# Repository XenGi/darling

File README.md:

![pcb][pcb]
![3d model front][3d-front]
![3d model back][3d-back]

darling
=======

FTDI helper for the future. With FT230X, blinky lights and USB-C! Also potentially the tinyest USB-C to Serial adapter in the world. :smiley:

__Got a smaller USB-C to serial adapter? Please send me a link!__

BOM
---

| Part                 | Qty | Pkg   | Ref    | Description       | Mouser | LCSC |
| -------------------- | -   | ----- | ------ | ----------------- | ------ | ---- |
| Hirose CX70M-24P1    | 1   | -     | J1     | USB-C Receptacle  | [798-CX70M-24P1](https://eu.mouser.com/ProductDetail/Hirose-Connector/CX70M-24P1?qs=NniTrqY%252BJ%252BUR9QssvRGPwA%3D%3D) | [C778726](https://www.lcsc.com/product-detail/C778726.html) |
| -                    | 1   | -     | J2     | Pin Header        | [571-826947-5](https://eu.mouser.com/ProductDetail/TE-Connectivity/826947-5?qs=xF5SkmKSM76JMcUnQ8djKQ%3D%3D) | [C6332198](https://www.lcsc.com/product-detail/C6332198) |
| FTDI FT230XQ-R       | 1   | QFN16 | U1     | USB-Serial IC     | [895-FT230XQ-R](https://eu.mouser.com/ProductDetail/FTDI/FT230XQ-R?qs=Gp1Yz1mis3VvmXwyDmIHOg%3D%3D) | [C128629](https://www.lcsc.com/product-detail/C128629) |
| -                    | 1   | 0603  | D1     | Red RX LED        | [710-150060GS75000](https://eu.mouser.com/ProductDetail/Wurth-Elektronik/150060GS75000?qs=LlUlMxKIyB0UYkq5lDO8nA%3D%3D) | [C965804](https://www.lcsc.com/product-detail/C965804) |
| -                    | 1   | 0603  | D2     | Green TX LED      | [710-150060RS75000](https://eu.mouser.com/ProductDetail/Wurth-Elektronik/150060RS75000?qs=LlUlMxKIyB3QnmZ3fw%2FVCA%3D%3D) | [C965799](https://www.lcsc.com/product-detail/C965799) |
| -                    | 2   | 0402  | R1, R2 | 27 Ohm Resistor   | [652-CR0402FX-27R0GLF](https://eu.mouser.com/ProductDetail/Bourns/CR0402-FX-27R0GLF?qs=SFHnMgm9IsxG%252BvpJZf0h2g%3D%3D) | [C138021](https://www.lcsc.com/product-detail/C138021) |
| -                    | 2   | 0402  | R3, R4 | 270 Ohm Resistor  | [652-CR0402FX-2700GLF](https://eu.mouser.com/ProductDetail/Bourns/CR0402-FX-2700GLF?qs=SFHnMgm9IsyXrY3JqhOnHQ%3D%3D) | [C163474](https://www.lcsc.com/product-detail/C163474) |
| -                    | 2   | 0402  | R5, R6 | 5.1 kOhm Resistor | [652-CR0402FX-5101GLF](https://eu.mouser.com/ProductDetail/Bourns/CR0402-FX-5101GLF?qs=ePR1ZvdkOKImkuXR%2F%2FtvtA%3D%3D) | [C105873](https://www.lcsc.com/product-detail/C105873) |
| -                    | 1   | 0402  | C1     | 10 nF Capacitor   | [80-C0402C103K3R7867](https://eu.mouser.com/ProductDetail/KEMET/C0402C103K3RAC7867?qs=2QcrrtqkWlmbWpEppaNgjw%3D%3D) | [C272878](https://www.lcsc.com/product-detail/C272878) |
| -                    | 2   | 0402  | C2, C4 | 100 nF Capacitor  | [81-GRM155C71H104JE9J](https://eu.mouser.com/ProductDetail/Murata-Electronics/GRM155C71H104JE19J?qs=QzBtWTOodeUR0Y4f0k0Zww%3D%3D) | [C541464](https://www.lcsc.com/product-detail/C541464) |
| -                    | 1   | 0402  | C3     | 4.7 uF Capacitor  | [81-GRM15C61E475ME15J](https://eu.mouser.com/ProductDetail/Murata-Electronics/GRM155C61E475ME15J?qs=By6Nw2ByBD02p8xq06vhEQ%3D%3D) | [C368809](https://www.lcsc.com/product-detail/C368809) |
| -                    | 2   | 0402  | C5, C6 | 47 pF Capacitor   | [81-GRT1555C1H470FA2D](https://eu.mouser.com/ProductDetail/Murata-Electronics/GRT1555C1H470FA02D?qs=RcG8xmE7yp3he2Sm3%2FOw%252Bg%3D%3D) | [C527009](https://www.lcsc.com/product-detail/C527009) |
| Laird MI0805K601R-10 | 1   | 0805  | FB1    | Ferrite Bead      | [875-MI0805K601R-10](https://eu.mouser.com/ProductDetail/Laird-Performance-Materials/MI0805K601R-10?qs=bbdZqDPQhEXXIHxc191aOg%3D%3D) | [C21286](https://www.lcsc.com/product-detail/C21286) |

See [Octopart][octopart] for a detailed list with links.
With current prices this totals to ~4.50€ just for parts excluding costs for the PCB manufacturing. If you need a PCB, just ask. I have lots of them. :)

Schematics
----------

![schematics][schema]

Create Gerber files
-------------------

Export the gerber and drill files from KiCAD to a subdir like `gerber`. To create a ZIP file with the needed gerber files for a PCB fab:

```
cd gerber
zip darling.zip *.gbr *.drl
```

I recommend [JLCPCB][jlcpcb]. It's the cheapest way to get the PCBs and they offer decent quality.
You can directly order it at [PCBWay][pcbway]. They've got some nice matte black PCBs!
If you want purple PCBs you can also use [OSHPark][oshpark].
If you want it faster and you're in Germany/EU I uploaded it to [Aisler][aisler] to.

[![pcb top][oshpark_darling_top] ![pcb bottom][oshpark_darling_bottom]][oshpark]

---

_Made with :heart: and aliexpress_

[pcb]: https://gitlab.com/xengi/darling/raw/master/darling_pcb.png
[3d-front]: https://gitlab.com/xengi/darling/raw/master/darling_3d_front.png
[3d-back]: https://gitlab.com/xengi/darling/raw/master/darling_3d_back.png
[schema]: https://gitlab.com/xengi/darling/raw/master/darling_schema.png
[octopart]: https://octopart.com/bom-tool/4VikRkAe
[jlcpcb]: https://jlcpcb.com/
[pcbway]: https://www.pcbway.com/project/shareproject/Darling_Rev4_f9889cb6.html
[oshpark_darling_top]: https://644db4de3505c40a0444-327723bce298e3ff5813fb42baeefbaa.ssl.cf1.rackcdn.com/4cf1ffcfeee0332e9eda92195310da6b.png
[oshpark_darling_bottom]: https://644db4de3505c40a0444-327723bce298e3ff5813fb42baeefbaa.ssl.cf1.rackcdn.com/1f266f38a687f960f46bc39729592b03.png
[oshpark]: https://oshpark.com/shared_projects/s8UnAcGC
[aisler]: https://aisler.net/p/NFTQABKA

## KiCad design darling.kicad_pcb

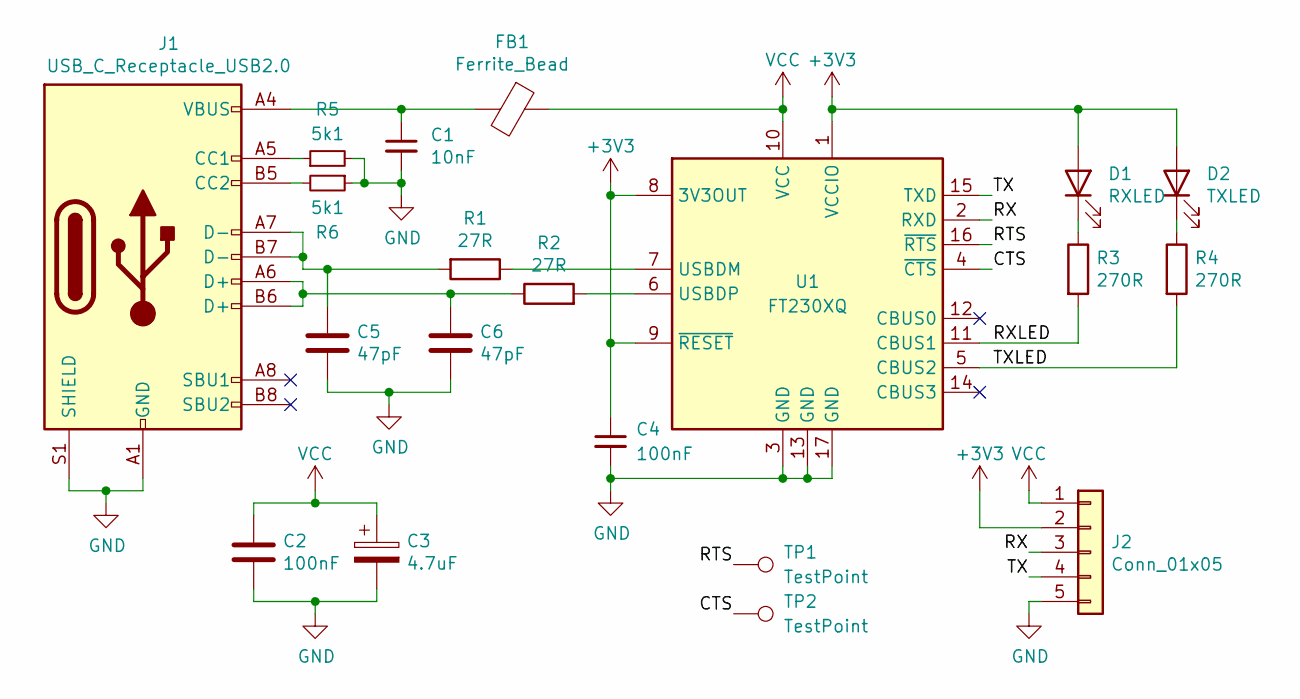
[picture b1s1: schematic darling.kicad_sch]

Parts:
C1: 10nF; C_0402_1005Metric; LCSC C272878
C2, C4: 100nF; C_0402_1005Metric; LCSC C541464
C3: 4.7uF; C_0402_1005Metric; LCSC C368809
C5, C6: 47pF; C_0402_1005Metric; LCSC C527009
D1: RXLED; LED_0603_1608Metric_Pad1.05x0.95mm_HandSolder; LCSC C965804
D2: TXLED; LED_0603_1608Metric_Pad1.05x0.95mm_HandSolder; LCSC C965799
FB1: Ferrite_Bead; L_0805_2012Metric_Pad1.15x1.40mm_HandSolder; LCSC C21286
J1: USB_C_Receptacle_USB2.0; CX70M-24P1; LCSC C778726
J2: Conn_01x05; PinHeader_1x05_P2.54mm_Horizontal; LCSC C6332198
R1, R2: 27R; R_0402_1005Metric; LCSC C138021
R3, R4: 270R; R_0402_1005Metric; LCSC C163474
R5, R6: 5k1; R_0402_1005Metric; LCSC C105873
TP1, TP2: TestPoint; TestPoint_Pad_D1.0mm
U1: FT230XQ; QFN-16-1EP_4x4mm_P0.65mm_EP2.5x2.5mm; LCSC C128629

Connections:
+3V3: C4.1, D1.2 (A), D2.2 (A), J2.2, U1.1 (VCCIO), U1.8 (3V3OUT), U1.9 (~RESET)
/CTS: TP2.1, U1.4 (~CTS)
/RTS: TP1.1, U1.16 (~RTS)
/RX: J2.3, U1.2 (RXD)
/RXLED: R3.2, U1.11 (CBUS1)
/TX: J2.4, U1.15 (TXD)
/TXLED: R4.2, U1.5 (CBUS2)
GND: C1.2, C2.2, C3.2, C4.2, C5.2, C6.2, J1.A1 (GND), J1.A12 (GND), J1.B1 (GND), J1.B12 (GND), J1.S1 (SHIELD), J2.5, R5.2, R6.1, U1.3 (GND), U1.13 (GND), U1.17 (GND)
unnamed: C1.1, FB1.2, J1.A4 (VBUS), J1.A9 (VBUS), J1.B4 (VBUS), J1.B9 (VBUS)
unnamed: C5.1, J1.A7 (D-), J1.B7 (D-), R1.2
unnamed: C6.1, J1.A6 (D+), J1.B6 (D+), R2.1
unnamed: D1.1 (K), R3.1
unnamed: D2.1 (K), R4.1
unnamed: J1.A5 (CC1), R5.1
unnamed: J1.B5 (CC2), R6.2
unnamed: R1.1, U1.7 (USBDM)
unnamed: R2.2, U1.6 (USBDP)
VCC: C2.1, C3.1, FB1.1, J2.1, U1.10 (VCC)

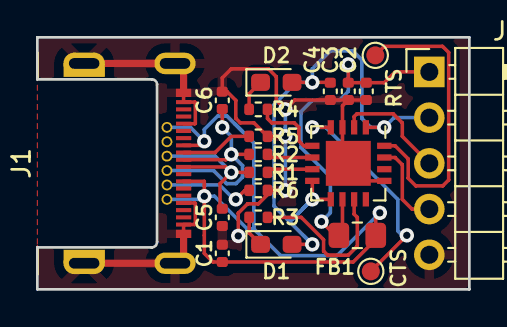
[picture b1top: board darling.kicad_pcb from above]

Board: 2 copper layers, 24.0 x 14.0 mm, 20 parts (0 on the bottom side), 18 nets.

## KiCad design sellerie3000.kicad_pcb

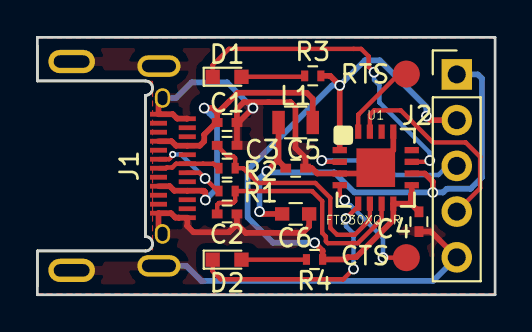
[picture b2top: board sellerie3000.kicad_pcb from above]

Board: 2 copper layers, 25.4 x 14.3 mm, 18 parts (0 on the bottom side), 16 nets.

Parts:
C1: 10nF; C_0402
C2, C3: 47pF; C_0402
C4, C5: 100nF; C_0402
C6: 4.7uF; C_0603
CTS: CTS; Measurement_Point_Round-SMD-Pad_Small
D1: RX; LED_0603
D2: TX; LED_0603
J1: USB_C_Receptacle; DX07B024JJ3
J2: Conn_01x05; Pin_Header_Straight_1x05_Pitch2.54mm
L1: Ferrite_Bead; L_0805
R1, R2: 27R; R_0402
R3, R4: 270R; R_0402
RTS: RTS; Measurement_Point_Round-SMD-Pad_Small
U1: FT230XQ-R; QFN16

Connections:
3V3: C4.1, J2.2, R3.1, R4.1, U1.1, U1.8, U1.9
/CBUS1: D1.1, U1.11
/CBUS2: D2.1, U1.5
/CTS: CTS.1, U1.4
/RTS: RTS.1, U1.16
/USBDM: C2.1, R1.1, U1.7
/USBDP: C3.1, R2.1, U1.6
GND: C1.2, C2.2, C3.2, C4.2, C5.2, C6.2, J1.A1, J1.A12, J1.B1, J1.B12, J1.S1, J2.5, U1.3, U1.13, U1.17
unnamed: C1.1, J1.A4, J1.A9, J1.B4, J1.B9, L1.2
unnamed: D1.2, R3.2
unnamed: D2.2, R4.2
unnamed: J1.A6, J1.B6, R2.2
unnamed: J1.A7, J1.B7, R1.2
RX: J2.3, U1.2
TX: J2.4, U1.15
VCC: C5.1, C6.1, J2.1, L1.1, U1.10

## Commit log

2018-06-17 finished design
2018-06-17 replaced comma with dots
2018-06-24 wow much update many unfinished
2018-06-25 nearly done
2018-06-25 measurements added
2018-10-28 Add LICENSE
2019-03-26 refactured to version 2; new usb receptacle; even tinier
2019-03-26 README updated
2019-03-26 trying to remove the 2nd git repo o0
2019-03-26 begone! strange repo!
2019-03-26 smaler images
2019-03-27 artwork improved
2019-04-19 switched LEDs
2019-04-20 reroute some parts
2019-04-20 changed drc rules
2019-04-20 fixed #4 usb-c is now reversable
2019-04-20 images updates
2019-04-20 removed J1 label
2019-04-20 downsized images
2019-04-20 something changed
2019-04-20 drc runs again. woop woop!
2019-04-20 added updated gerber files
2019-04-20 oshpark links updated
2019-05-01 Add new file
2019-05-01 Added to kitspace
2019-05-02 bom added in tsv format
2019-05-02 mouser ids added
2019-05-02 bom fixed
2019-05-02 renaming kitspace file
2019-05-02 aisler added to readme; bom updated
2023-07-10 Add missing CC resistors
2023-07-10 update pictures
2023-11-28 minimal touches
2023-11-28 PCB finalized
2023-11-28 final rev 4
2023-11-28 update readme and images
2023-11-29 raytracing images added
2023-12-07 add flake
2023-12-30 update flake
2024-01-04 add LCSC and Mouser part numbers
2024-01-04 update kitspace
2024-01-04 update pin header
2024-03-17 convert to kicad 8 format
2024-03-17 add pcbway link
